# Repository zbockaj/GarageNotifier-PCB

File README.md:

# GarageNotifier-PCB
Helium-network device for reporting open/closed status of (garage) door.

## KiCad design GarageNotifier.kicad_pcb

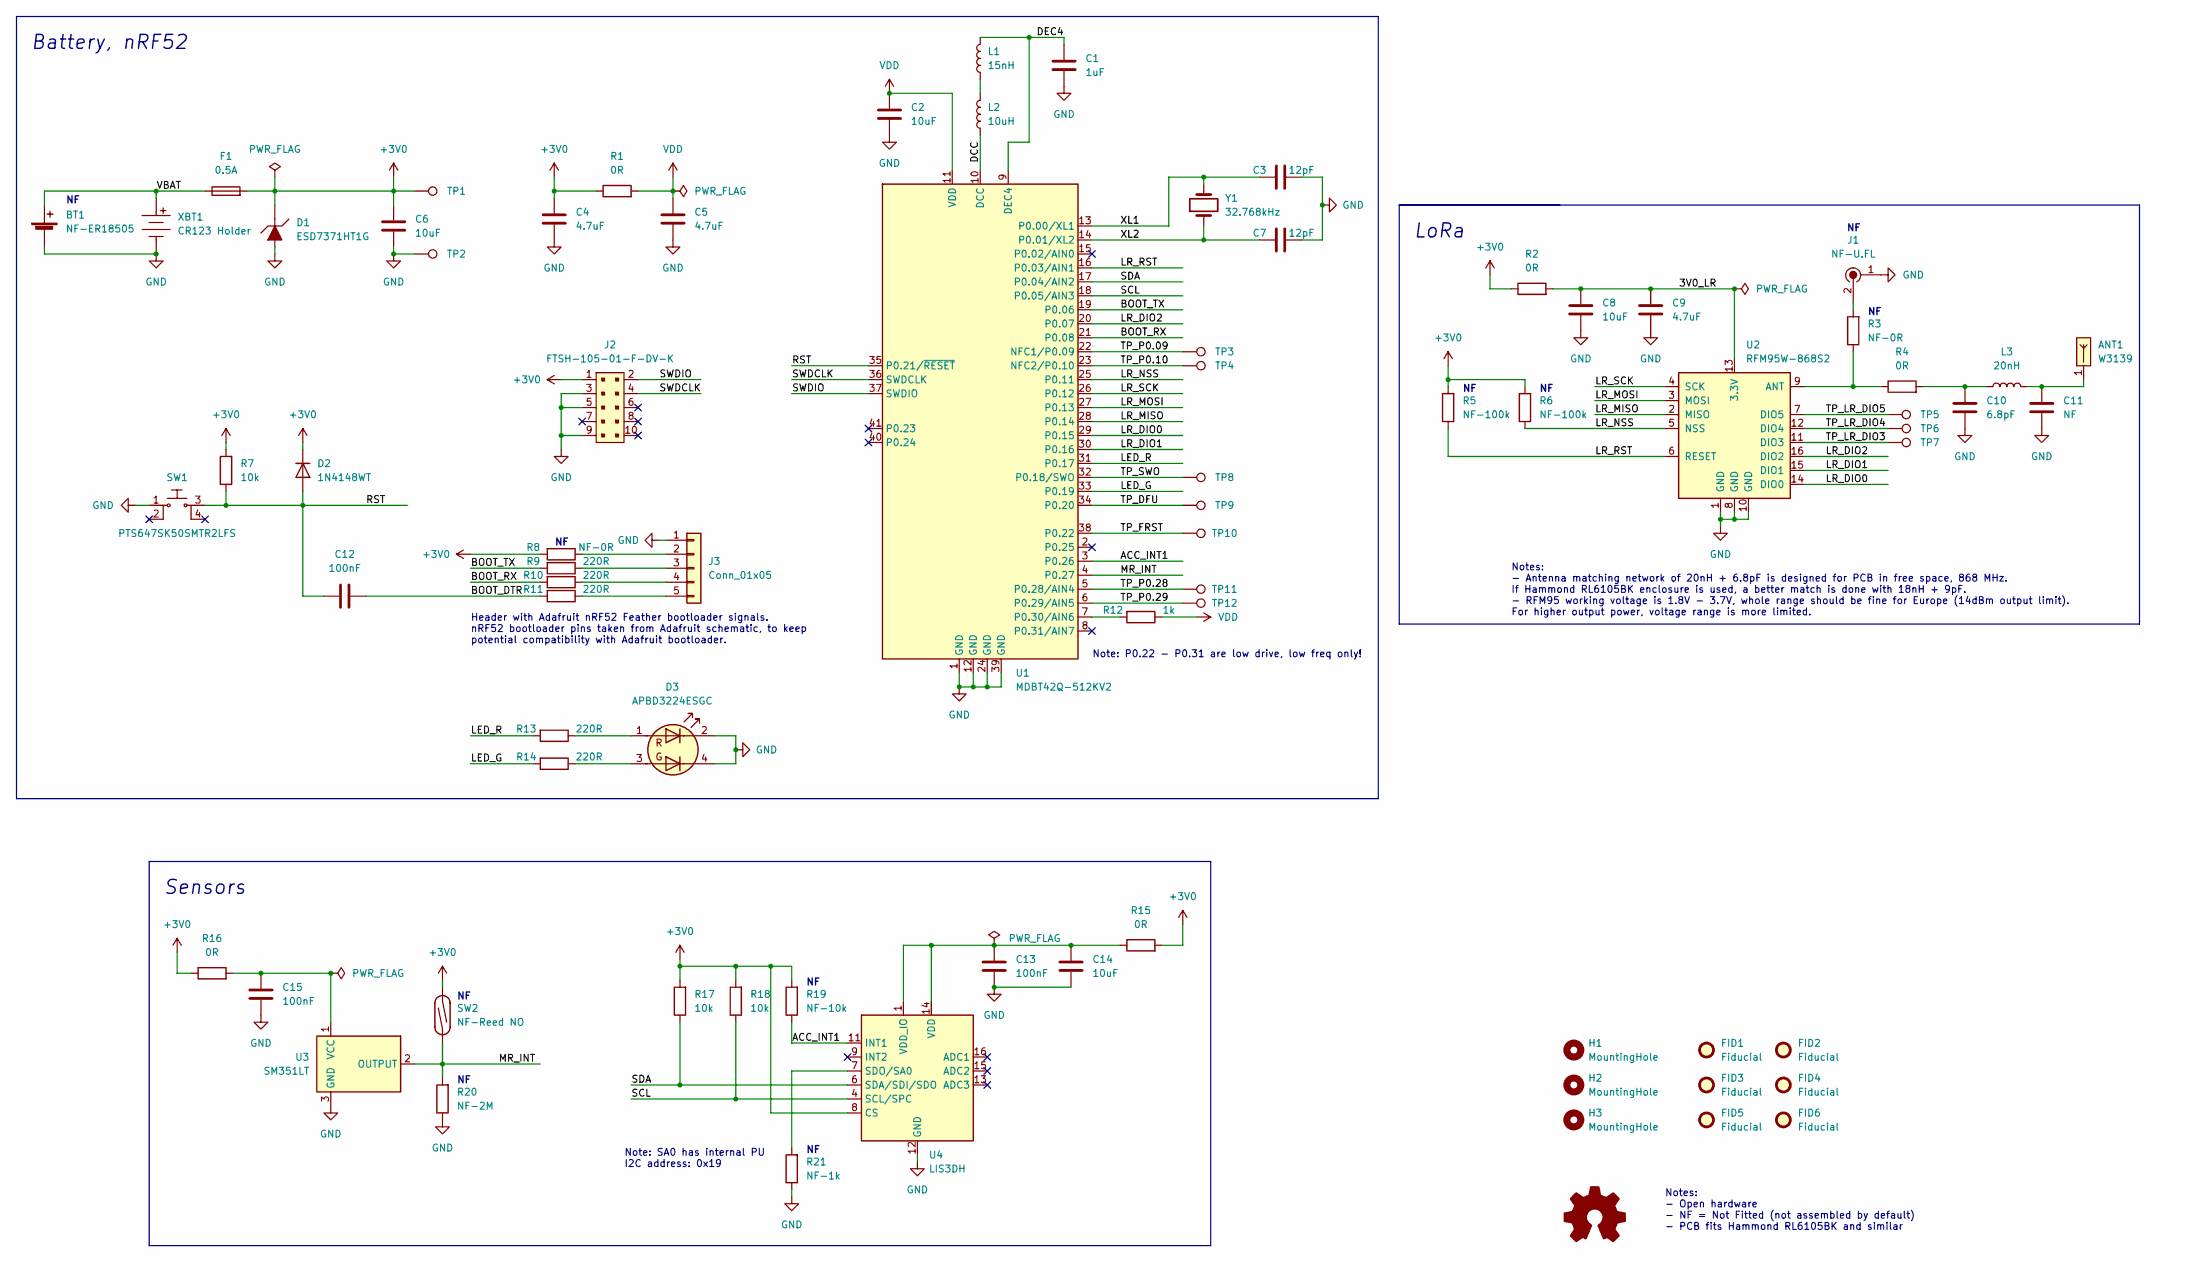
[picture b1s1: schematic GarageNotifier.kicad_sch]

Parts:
ANT1: W3139; MPN W3139
BT1: NF-ER18505; ER18505; MPN ER18505
C1: 1uF; C_0402_1005Metric
C2, C6, C8, C14: 10uF; C_0603_1608Metric
C3, C7: 12pF; C_0402_1005Metric
C4, C5, C9: 4.7uF; C_0603_1608Metric
C10: 6.8pF; C_0603_1608Metric
C11: NF; C_0603_1608Metric
C12, C13, C15: 100nF; C_0603_1608Metric
D1: ESD7371HT1G; SOD-323; MPN ESD7371HT1G
D2: 1N4148WT; D_SOD-523; MPN 1N4148WT
D3: APBD3224ESGC; LED_Kingbright_APBD3224; MPN APBD3224ESGC-F01
F1: 0.5A; R_0603_1608Metric; MPN 0467.500NRHF
FID1, FID2, FID3, FID4, FID5, FID6: Fiducial; Fiducial_1mm_Mask2mm
H1, H2, H3: MountingHole; MountingHole_2.7mm_M2.5_ISO7380
J1: NF-U.FL; Coax_Conn_U.FL; MPN U.FL-R-SMT-1(10); Digi-Key_PN H11891CT-ND
J2: FTSH-105-01-F-DV-K; PinHeader_2x5_P1.27_SMD; MPN FTSH-105-01-F-DV-K; Digi-Key_PN SAM8796-ND
J3: Conn_01x05; PinHeader_1x05_P2.54mm_Vertical
L1: 15nH; L_0402_1005Metric; MPN LQG15HS15NJ02D
L2: 10uH; L_0603_1608Metric; MPN LQM18FN100M00D
L3: 20nH; L_0603_1608Metric; MPN LQW18AN20NG00D
R1, R2, R4, R15, R16: 0R; R_0603_1608Metric
R3, R8: NF-0R; R_0603_1608Metric
R5, R6: NF-100k; R_0603_1608Metric
R7, R17, R18: 10k; R_0603_1608Metric
R9, R10, R11, R13, R14: 220R; R_0603_1608Metric
R12: 1k; R_0603_1608Metric
R19: NF-10k; R_0603_1608Metric
R20: NF-2M; R_0603_1608Metric
R21: NF-1k; R_0603_1608Metric
SW1: PTS647SK50SMTR2LFS; MPN PTS647SK50SMTR2LFS
SW2: NF-Reed NO; MK15-B-2_Reed; MPN MK15-B-2
TP1, TP2, TP3, TP4, TP5, TP6, TP7, TP8, TP9, TP10, TP11, TP12: TestPoint; TestPoint_Pad_D1.5mm
U1: MDBT42Q-512KV2; MPN MDBT42Q-512KV2
U2: RFM95W-868S2; HOPERF_RFM9XW_SMD; MPN 109990166
U3: SM351LT; SOT-23; MPN SM351LT
U4: LIS3DH; ST_LGA-16_3x3mm; MPN LIS3DHTR
XBT1: CR123 Holder; Keystone_1051; MPN 1051
Y1: 32.768kHz; Crystal_SMD_3215-2Pin_3.2x1.5mm; MPN FC-135 32.7680KA-AC

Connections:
+3V0: C4.1, C6.1, D1.1 (A1), D2.1 (K), F1.2, J2.1, R1.1, R2.1, R5.2, R6.2, R7.2, R8.2, R15.2, R16.1, R17.2, R18.2, R19.2, SW2.2, TP1.1, U4.8 (CS)
/3V0_LR: C8.1, C9.1, R2.2, U2.13 (3.3V)
/ACC_INT1: R19.1, U1.3 (P0.26), U4.11 (INT1)
/BOOT_DTR: C12.1, R11.2
/BOOT_RX: R10.2, U1.21 (P0.08)
/BOOT_TX: R9.2, U1.19 (P0.06)
/DCC: L2.1, U1.10 (DCC)
/DEC4: C1.1, L1.2, U1.9 (DEC4)
/LED_G: R14.2, U1.33 (P0.19)
/LED_R: R13.2, U1.31 (P0.17)
/LR_DIO0: U1.29 (P0.15), U2.14 (DIO0)
/LR_DIO1: U1.30 (P0.16), U2.15 (DIO1)
/LR_DIO2: U1.20 (P0.07), U2.16 (DIO2)
/LR_MISO: U1.28 (P0.14), U2.2 (MISO)
/LR_MOSI: U1.27 (P0.13), U2.3 (MOSI)
/LR_NSS: R6.1, U1.25 (P0.11), U2.5 (NSS)
/LR_RST: R5.1, U1.16 (P0.03/AIN1), U2.6 (RESET)
/LR_SCK: U1.26 (P0.12), U2.4 (SCK)
/MR_INT: R20.2, SW2.1, U1.4 (P0.27), U3.2 (OUTPUT)
/RST: C12.2, D2.2 (A), R7.1, SW1.3, U1.35 (P0.21/~RESET)
/SCL: R18.1, U1.18 (P0.05/AIN3), U4.4 (SCL/SPC)
/SDA: R17.1, U1.17 (P0.04/AIN2), U4.6 (SDA/SDI/SDO)
/SWDCLK: J2.4, U1.36 (SWDCLK)
/SWDIO: J2.2, U1.37 (SWDIO)
/TP_DFU: TP9.1, U1.34 (P0.20)
/TP_FRST: TP10.1, U1.38 (P0.22)
/TP_LR_DIO3: TP7.1, U2.11 (DIO3)
/TP_LR_DIO4: TP6.1, U2.12 (DIO4)
/TP_LR_DIO5: TP5.1, U2.7 (DIO5)
/TP_P0.09: TP3.1, U1.22 (NFC1/P0.09)
/TP_P0.10: TP4.1, U1.23 (NFC2/P0.10)
/TP_P0.28: TP11.1, U1.5 (P0.28/AIN4)
/TP_P0.29: TP12.1, U1.6 (P0.29/AIN5)
/TP_SWO: TP8.1, U1.32 (P0.18/SWO)
/VBAT: BT1.1 (+), F1.1, XBT1.1
/XL1: C3.1, U1.13 (P0.00/XL1), Y1.2
/XL2: C7.1, U1.14 (P0.01/XL2), Y1.1
GND: BT1.2 (-), C1.2, C2.2, C3.2, C4.2, C5.2, C6.2, C7.2, C8.2, C9.2, C10.1, C11.1, C13.2, C14.2, C15.2, D1.2 (A2), D3.2 (K1), D3.4 (K2), J1.1, J2.3, J2.5, J2.9, J3.1, R20.1, R21.1, SW1.1, TP2.1, U1.1 (GND), U1.12 (GND), U1.24 (GND), U1.39 (GND), U2.1 (GND), U2.8 (GND), U2.10 (GND), U3.3 (GND), U4.5 (GND), U4.10 (GND), U4.12 (GND), XBT1.2
unnamed: ANT1.1 (FP), C11.2, L3.2
unnamed: C10.2, L3.1, R4.2
unnamed: C13.1, C14.1, R15.1, U4.1 (VDD_IO), U4.14 (VDD)
unnamed: C15.1, R16.2, U3.1 (VCC)
unnamed: D3.1 (A1), R13.1
unnamed: D3.3 (A2), R14.1
unnamed: J1.2, R3.2
unnamed: J3.2, R8.1
unnamed: J3.3, R9.1
unnamed: J3.4, R10.1
unnamed: J3.5, R11.1
unnamed: L1.1, L2.2
unnamed: R3.1, R4.1, U2.9 (ANT)
unnamed: R12.2, U1.7 (P0.30/AIN6)
unnamed: R21.2, U4.7 (SDO/SA0)
VDD: C2.1, C5.1, R1.2, R12.1, U1.11 (VDD)

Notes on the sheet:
Notes: - Antenna matching network of 20nH + 6.8pF is designed for PCB in free space, 868 MHz. If Hammond RL6105BK enclosure is used, a better match is done with 18nH + 9pF. - RFM95 working voltage is 1.8V - 3.7V, whole range should be fine for Europe (14dBm output limit). For higher output power, v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
Note: P0.22 - P0.31 are low drive, low freq only!
Notes: - Open hardware - NF = Not Fitted (not assembled by default) - PCB fits Hammond RL6105BK and similar
Sensors
Battery, nRF52
Header with Adafruit nRF52 Feather bootloader signals. nRF52 bootloader pins taken from Adafruit schematic, to keep potential compatibility with Adafruit bootloader.
Note: SA0 has internal PU I2C address: 0x19
LoRa

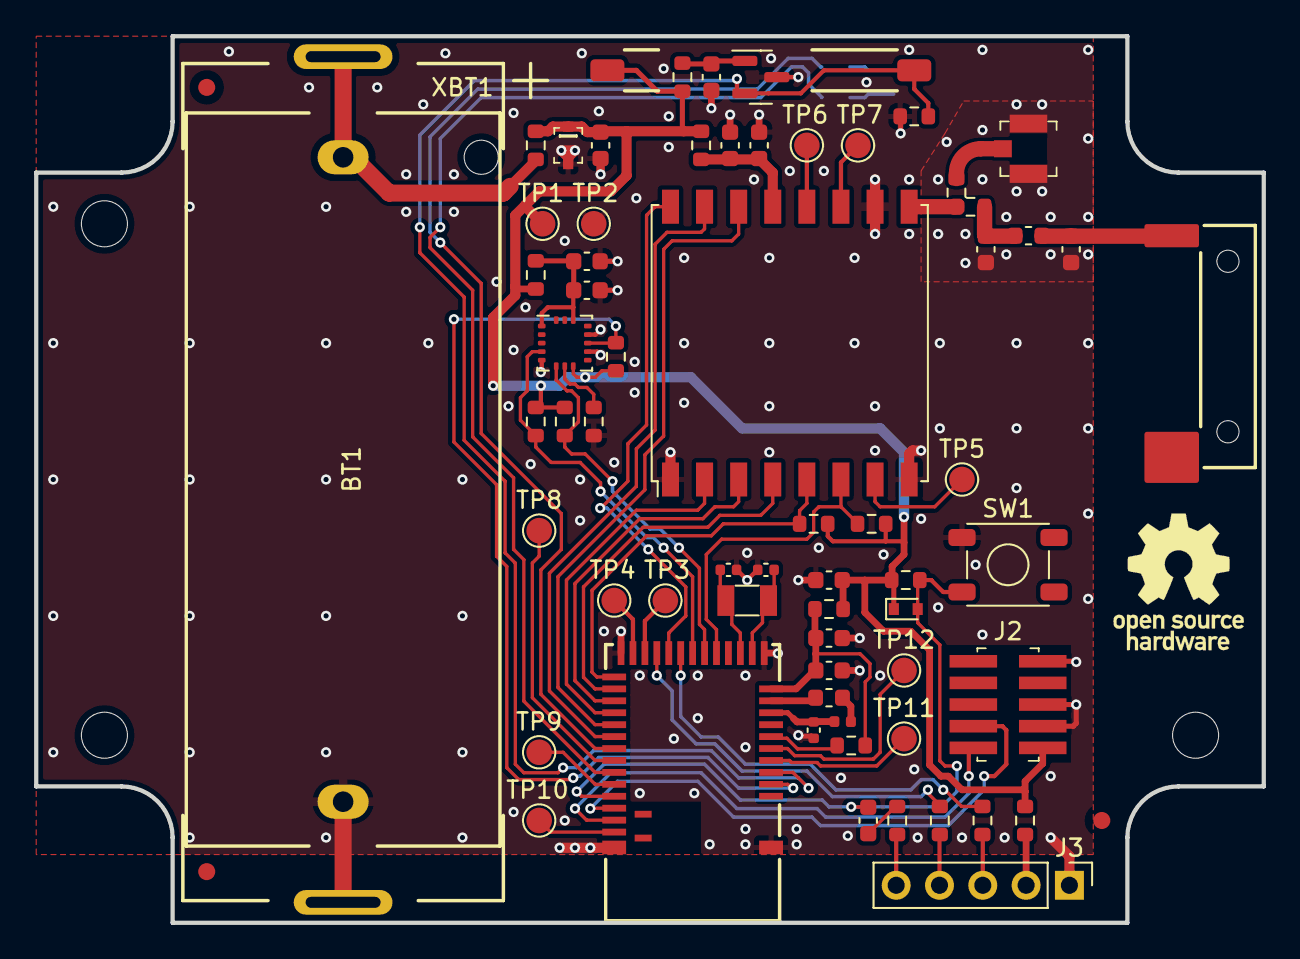
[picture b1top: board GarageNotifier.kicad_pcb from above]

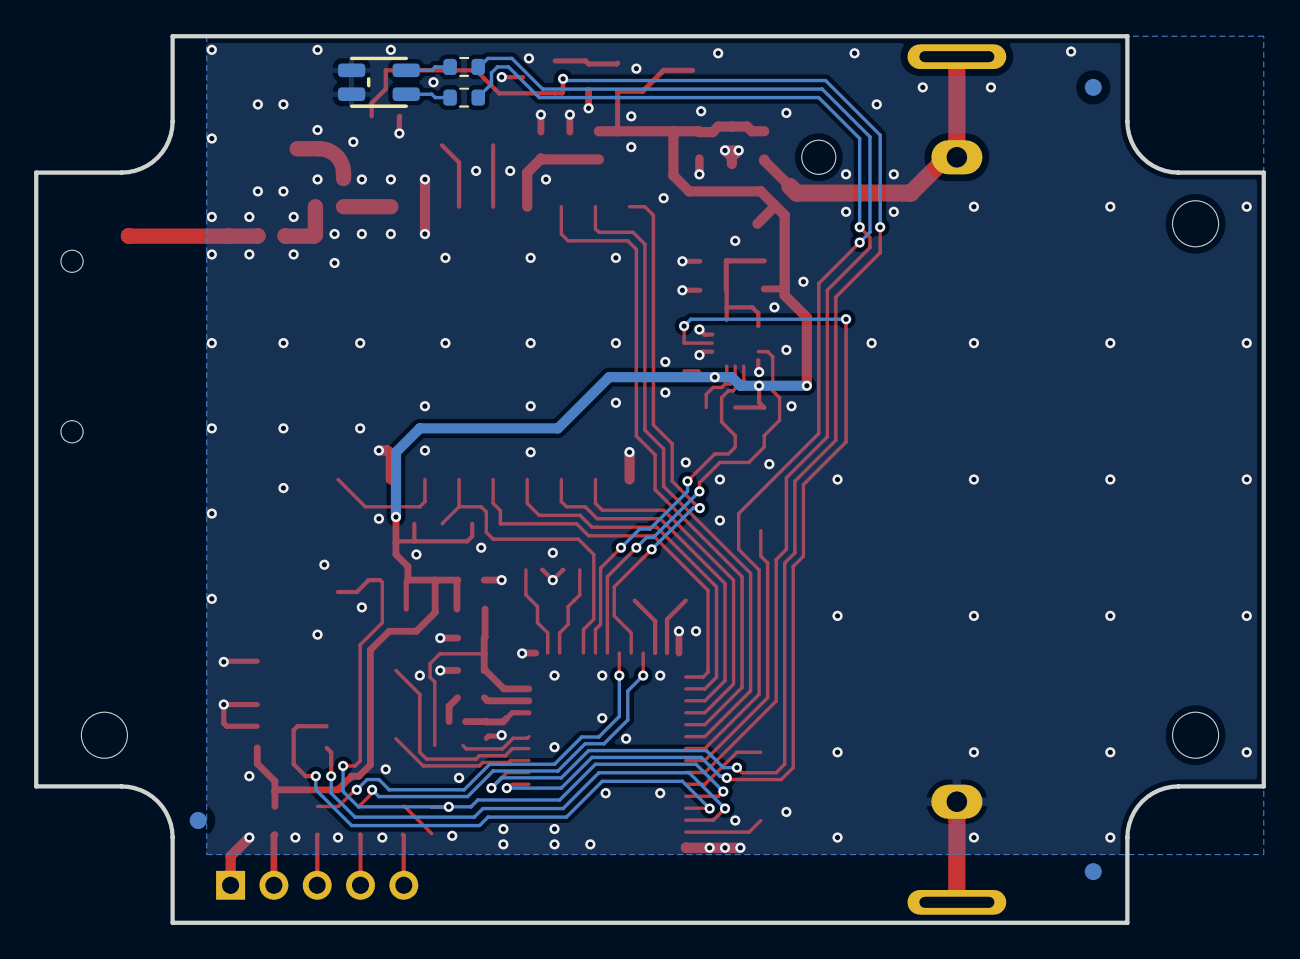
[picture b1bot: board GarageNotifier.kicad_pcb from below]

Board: 2 copper layers, 72.0 x 52.0 mm, 77 parts (6 on the bottom side), 54 nets.

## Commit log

2022-08-15 KiCad files added
2022-08-15 Added release files
    Added zip files with PCB production and assembling info used for JLCPCB. Removed digikey project library (now it is kicad global).
